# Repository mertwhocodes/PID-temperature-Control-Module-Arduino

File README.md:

# Heater-PID-Control-Module-

**Close loop PID Heater Control Module**

This module designed to control AC Clamp heater or any AC heater with PID algorithm.
That module use Max6675 Cold-Junction-Compensated K-Thermocoupleto-Digital Converter to mesure 
temperature of heater.First you have to include max6675.h on arduino ide.
# **Companent list**
- Max6675
- BTA-16 triac
- Moc3020
- Pc817
- D1208 rectifier
- K-type thermocouple
- 2x47k res
- 100 res
- 200 res
- 1k res
- 0.1µF con
# Installation 
> go get [github.com/merttuncell/Heater-PID-Control-Module-](https://github.com/merttuncell/Heater-PID-Control-Module- )

> add Max6675.h  arduino library from [ https://github.com/adafruit/MAX6675-library]( https://github.com/adafruit/MAX6675-library)
# Arduino Connection

# Pin Configuration

- **GND** - Ground
- **Frig** - Triger pin for Triac  
- **Z0** - AC Voltage ZeroOut dedection output pin high when [zero cross](https://en.wikipedia.org/wiki/Zero_crossing_control )  dedection
- **SO** - Serial Data Output For MAX6675
- **CS** - Ship Select Set CS low to enable the serial interface 
- **SCK** - Serial Clock Input 
- **VCC** - Positive Supply (3V-5.5V)

# Repository Contents

- **/Documentation** - Datasheets, additional product information

- **/Frimware** - Example code for Arduino

- **/Hardware** - Eagle design files(.brd, .sch)

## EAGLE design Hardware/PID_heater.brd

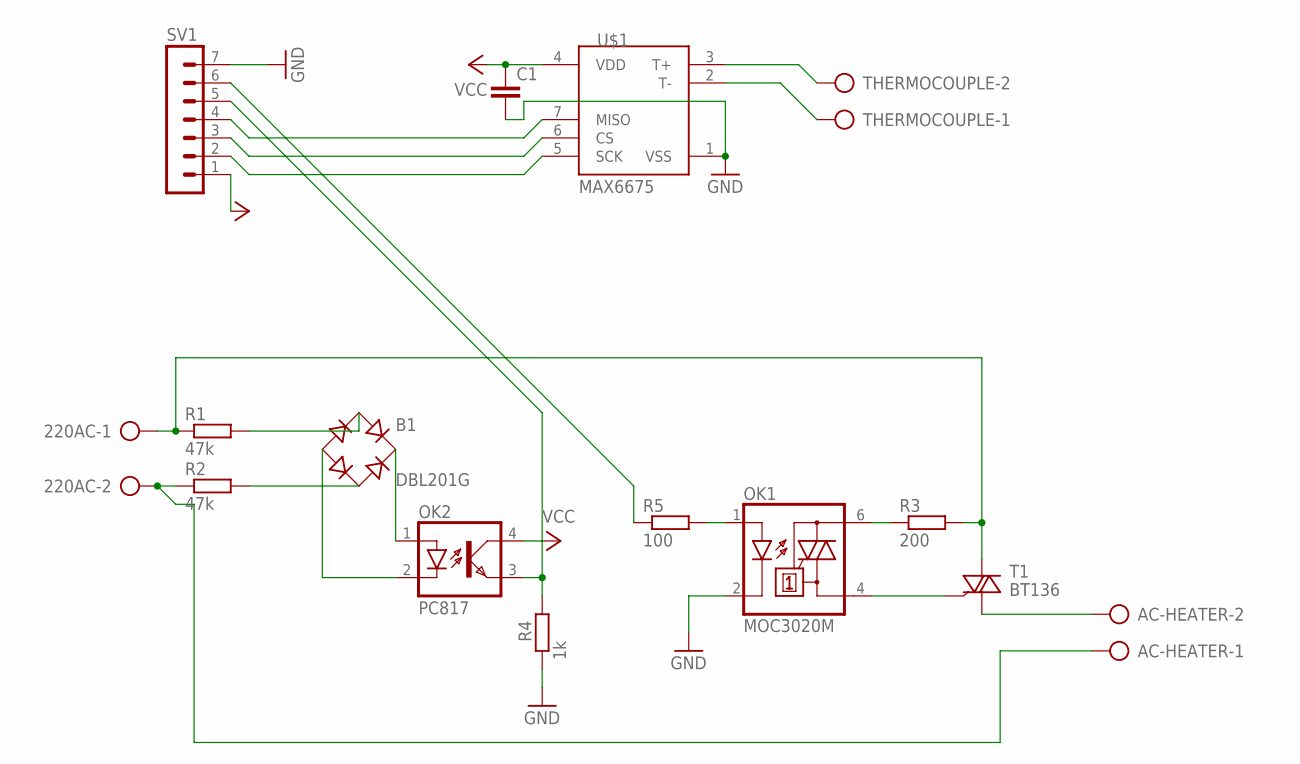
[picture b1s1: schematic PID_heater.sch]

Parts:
220AC: AK300/2
AC-HEATER: AK300/2
B1: DBL201G; DB
C1: 0.1u; C0805
OK1: MOC3020M; DIL06
OK2: PC817; DIL04
R1, R2: 47k; R0805
R3: 200; R0805
R4: 1k; R0805
R5: 100; R0805
SV1: MA07-1
T1: BT136; TO220AB
THERMOCOUPLE: AK300/2
U$1: MAX6675; SO08

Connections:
GND: C1.2, OK1.2 (C), R4.1, SV1.7, U$1.1 (VSS)
unnamed: OK1.6 (A2), R3.1
unnamed: 220AC.1, R1.1, R3.2, T1.2 (A2)
unnamed: 220AC.2, AC-HEATER.1, R2.1
unnamed: B1.AC1, R1.2
unnamed: B1.AC2, R2.2
unnamed: B1.+, OK2.1 (A)
unnamed: B1.-, OK2.2 (C)
unnamed: OK2.3 (EMIT), R4.2, SV1.5
unnamed: OK1.1 (A), R5.2
unnamed: OK1.4 (A1), T1.3 (G)
unnamed: THERMOCOUPLE.2, U$1.3 (T+)
unnamed: AC-HEATER.2, T1.1 (A1)
unnamed: THERMOCOUPLE.1, U$1.2 (T-)
unnamed: R5.1, SV1.6
unnamed: SV1.4, U$1.7 (MISO)
unnamed: SV1.3, U$1.6 (CS)
unnamed: SV1.2, U$1.5 (SCK)
VCC: C1.1, OK2.4 (COL), SV1.1, U$1.4 (VDD)

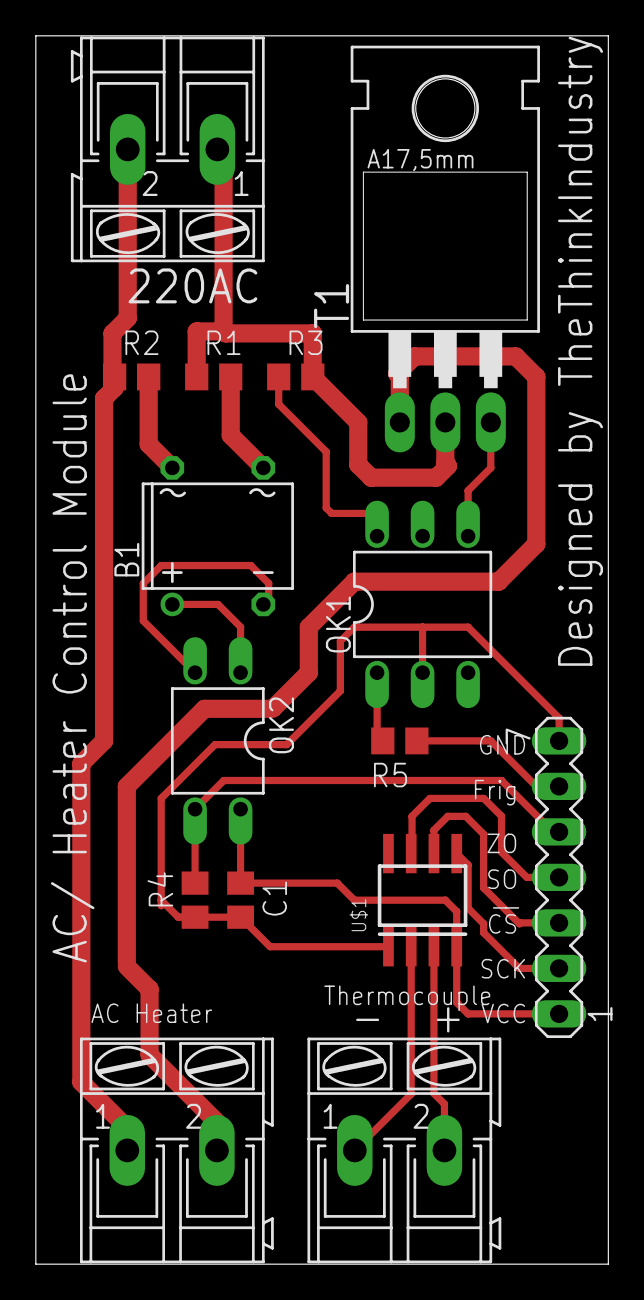
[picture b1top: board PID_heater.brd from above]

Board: 2 copper layers, 32.0 x 68.6 mm, 15 parts (0 on the bottom side), 19 nets.

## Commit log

2019-03-08 Designed
    PID Header Control Module
2019-03-08 yedek name change to backup
2019-03-08 Create PID.ino
    PID Kodları eklendi
2019-03-08 commands are deleted
2019-03-08 Set theme jekyll-theme-minimal
2019-03-08 commad deleted
2019-03-09 Wires width changed
    pin Names and TheThinkIndustry Logos Added
2019-03-09 R1-R2-R3 wires width changed
2019-03-09 logo location changed
2019-10-11 Reorganize
2019-10-11 datasheets added
